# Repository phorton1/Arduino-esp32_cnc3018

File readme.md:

# Yet another cnc3018 Grbl Controller with WiFi and a TFT touch UI

This project has been interesting and is a waypoint on my path of understanding
and developing CNC machine controllers.  It is difficult to explain the decision
making process that led me here, or why I think it has been worth the investment
of time to arrive at this point, but I will try to touch on the main points.

Let's just start by saying I had *CNC fever*.  It started with *robots* but then
I had some stepper motors sitting around, and I wanted to make *something*, so
I built the **vMachine**.  While I was doing that I ordered a bunch of stuff to
make a variety of machines, including ordering two copies of the cheapest chinese 3018 CNC
machines I could find.

I had already long ago decided that I was going to use the ESP32 and (at that
time) the Grbl_Esp32 codebase for my machines.   The lure of a $5 dual processor
240Mhz SBC with Wifi and BT is just too much!   No way was I gonna use the Arduino
based controller that came with the machines.  So I was thinking about that the
entire time I was developing the vMachine.

Grbl_Esp32 was subsequently renamed to FluidNC, and I subsequently forked and
modified it to be usable as an extensible Arduino library. I had already also
started TFT UI development, and so these diverse aspects came together during
this project.

For me, one of the most interesting things about this project is the fact that
I used a prototype (breadboard) circuit while developing the machine to **mill
a controller board** for the machine itself!

Today I am just writing a quick readme to show off some of the machine's features
and steps in it's development.

## Prototype Circuit

I use these cool breadboards from [5e Board](https://www.5eboard.com/product-category/5e-circuit-boards/)
that allow me to create more complex and secure prototypes than with a normal breadboard.
Even then I decided early on that the spindle motor control and power supply should be on
a separate board, so I designed and implemented those parts on perf board.  They are visible
in the above photo.

The "test leads" in the above photo are for the z-axis **probe** which plays into the
development of the machine itself as the probe is used to develop the **mesh** for leveling
which is needed to obtain the z accuracy to mill the PC board.

## Limit Switches

The very first thing that everyone does to stock 3018's is adds limit switches.
So I 3D printed some mounts and stuck some limit switches on the machine. For
X and Y I just use the most ubiquitously available (cheapest!) switches, though
a bit large.  I went through multiple iterations on the Z axis, starting with
micro switches, but then relenting to using small (more expensive) lever switches.

Everything in grey plastic is my 3D printed additions to the machine (the black
plasatic is the original stuff).  The zAxis has a housing around the switches,
and an adjustable offset at the bottom (limit).  All the wires are shielded.

For the X and Y axis I originally started by using crimp on connectors that were
exposed, but didn't like them.  They kept falling off and the connectors were
too large for the wire I was using, so I 3D printed and constsructed my own connectors
using some thin brass sheet I've had sitting around for 20 years,

The crimp connectors were loose and easily fell off if you bumped them.
These connectors are secured with screws to ensure they don't fall off!

## Initial Sensor Board

I found pretty quickly that even with the nice breadboards, I was having
problems with the switches becasuse the leads on the resistors are small
and don't make good contact with breadboards.  So I created a perf board
version with the 74HC165 IO multiplexer chip and plugged it into the
breadboard:

## Milling the Controller Board

So, generally I got it working, but I was really anxious to eliminate the breadboard
and put a soldered board in place.   I was still getting problems due to the breadboard
and bad connections.

I had to learn a lot.  Spent time in  KiCad and Flatcam.   Designed it 10 times lol.
Cut some prototypes.  Learned a bit about applying and using green UV Solder Resist
Epoxy.

Finally got to where the following sequences of images looks practical :-)

1 - mill the board

In the end I had a pretty nice circuit board.  I will drill the holes after
doing the epoxy, so I then painted it with the green epoxy and exposed it
to the sun to cure the epoxy.

2 - mill the epoxy

OK, so I won't do this again!   It worked on this (v04) board, but subsquently
proved way too touchy to try to mill the UV epoxy off.  The copper layer is only
35/1000's of a millimeter ... like 2/1000's of an inch ... thick.   Even though
I added **mesh levelling** to the project, it is still nearly impossible to get
accurate enough to mill off the epoxy and NOT destroy the copper pads underneath.

The second photo above is actually a failure on an attempt to mill v05.
Most of the pads were destroyed because I was off by 1/100th of a millimeter!
Nonetheless it worked for this (V04) board and in the end I decided to use
V04 and move on.

I have ordered a UV laser.  My next idea is to expose the UV epoxy with the UV
laser on the cnc machine.  Photo masks are a bit complicated to work with!

3 - populate the board

Then it was pretty easy to solder on the headers, components, etc, and
I had a populated board.  It worked pretty much the first time!

I took a moment to take a photo of it with a light behind because it looks neat!

## Adding the touch screen

I put the board in the machine, and then used the machine to cut
another small circuit board to be used as a connector for the touch
screen:

After 3D printing an enclosure for it, and attaching it to the machine
(and reprinting it to add 5 ws2812b LEDs) I decided to write this page

Here is the final machine:

LOL, it still has the copper board from which I milled the LCD connector
on the work surface :-)

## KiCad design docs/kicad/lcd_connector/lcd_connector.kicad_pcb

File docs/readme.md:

# esp32_cnc3018 - Yet another cnc3018 Grbl Controller with WiFi and a TFT touch UI

**Home** --
**[History](history.md)** --
**[Hardware](hardware.md)** --
**[Electronics](electronics.md)** --
**[Software](software.md)** --
**[Installation](installation.md)** --
**[Version2](version2.md)**

esp32_cnc3018 is my implementation of an inexpensive 3-axis CNC machine that
makes use of the **ESP32** processor.  Essentially I bought the cheapest
3-axis CNC machine I could find on [Ebay](https://www.ebay.com/itm/392298131168), and then designed and implemented
my own controller board, limit switches, and extensions to that machine.

The ESP32 can easily be programmed from within the
Arduino development environment and has *dual cores*, runs at *240 Mhz* (as opposed to
the Arduino at 16Mhz) and comes with *520KB* (as opposed to 2KB) *of RAM*.  In addition
the ESP32 includes full onboard **WiFi and Bluetooth** capabilities, and can be had for
$5, or about half the price of a genuine Arduino.

Therefore my *primary design decision* was to base this, and my future CNC projects,
on an ESP32 processor.

**TODO: - VIDEO - introduction to the esp32_cnc3018**

TODO: Better picture of current esp32_cnc3018 (rename to Esp32_cnc3018)

The esp32_cnc3018 project is the 2nd machine in the line of open source
CNC machines I have created and published.  It provides a number of
features not commonly available in the lowest priced machines.

esp32_cnc3018 includes a full **Web Browser User Interface** so that it can be
controlled wirelessly from your phone or computer via **WiFi**.  It can also be controlled
via the **serial port** on the ESP32, via **Telnet** on port 23, or via **Bluetooth**
for usage with commonly available gcode sender programs.
Finally, it can also store gcode files on the optional **SD Card** and run jobs entirely
locally, right on the ESP32, via the optional
[**Touch Screen User Interface**](https://github.com/phorton1/Arduino-libraries-FluidNC_UI)
, without involving any other devices.

This repository includes all of the files and information needed to modify
a stock entry level CNC 3018 machine as I have. It includes the files needed to
**3D print** the plastic parts, as well as the underlying Fusion 360 designs
if you need or want to modify the 3D printed parts. It includes all of the **schematics**
and information needed to breadboard or otherwise create the electronic circuits,
as well as the KiCad files behind those, and the Flatcam and GCode files I used to
mill my own **circuit boards** for this machine.

This project continues a **general approach** to
building ESP32 based CNC machines of various types.
It is entirely based on the next generation
[FluidNC](https://github.com/bdring/FluidNC)
project, a hugely important codebase that I have
forked and modified slightly so-as to better be able build projects
within the Arduino IDE development environment.

<br>

## Documentation

The documentation starts with this page, and includes the following additional
pages:

- **[History](history.md)** - my personal historical **perspectives** and
  photos of the development process for the esp32_cnc3018 machine
- **[Hardware](hardware.md)** - shows the physical
  modifications to CNC 3018
- **[Electronics](electronics.md)** - the **schematics** and home made circuit
  boards for the machine.
- **[Software](software.md)** - describes the **software** architecture of
  esp32_cnc3018 and FluidNC
- **[Installation](Installation.md)** - instructions on **building** and installing
  the esp32_cnc3018 firmware onto the ESP32 using the Arduino IDE environment.

<br>

## Please Also See

Please also see my previous CNC machine based on the same architecture,
my implementation of a V-Plotter, the
[**vMachine**](https://github.com/phorton1/Arduino-_vMachine),
built entirely from scratch.

These "machines"  are relatively small INO programs.  They are built on top of a
number of other libraries that provide the bulk of the functionality.

- [**FluidNC**](https://github.com/phorton1/Arduino-libraries-FluidNC) - the next generation **ESP32 GRBL** machine
- [**FluidNC_UI**](https://github.com/phorton1/Arduino-libraries-FluidNC_UI) - a *touch screen user interface* for FluidNC
- [**FluidNC_Extensions**](https://github.com/phorton1/Arduino-libraries-FluidNC_Extensions) - some extensions to FluidNC

The core of the machine, the GRBL (g-code) interpreter, is based on the
[**FluidNC**](https://github.com/phorton1/Arduino-libraries-FluidNC)
library.  The operational details of the machine, what g-codes
are supported, the basic serial command protocol, the wifi and webserver,
the machine configuration, and most functional aspects of the machine are
provided by this library.

On top of FluidNC I have built
[**FluidNC_UI**](https://github.com/phorton1/Arduino-libraries-FluidNC_UI),
the *touch screen user interface*, as a library that can optionally
be used in ESP32 CNC projects.
Please see this library for a **description of the *User Interface***.

I have also added a
[**FluidNC_Extensions**](https://github.com/phorton1/Arduino-libraries-FluidNC_Extensions)
library that contains a number
of features that are used in this, and other machines based on this system.
This library contains methods and objects to abstract and extend the FluidNC
core.  Specific contents at this time include:

- some easy to use debug/info/error **output methods**
- methods to abstract the **state** of the FluidNC machine
- methods to abstract **control** of the FluidNC machine
- methods to supplement the FluidNC **configuration** system, and
- an implementation of **mesh bed levelling** as used in this esp32_cnc3018 machine

<br>

## Credits and License

This library is licensed under the
[GNU General Public License v3.0](https://github.com/phorton1/Arduino-esp32_cnc3018/tree/master/LICENSE.TXT)

**Credits**

- To **bdring** and the **FluidNC Team**

<br>
<hr>
<div style="text-align: right">
<a href='history.md'>NEXT</a><i> - more about esp32_cnc3018 ...</i>
</div>

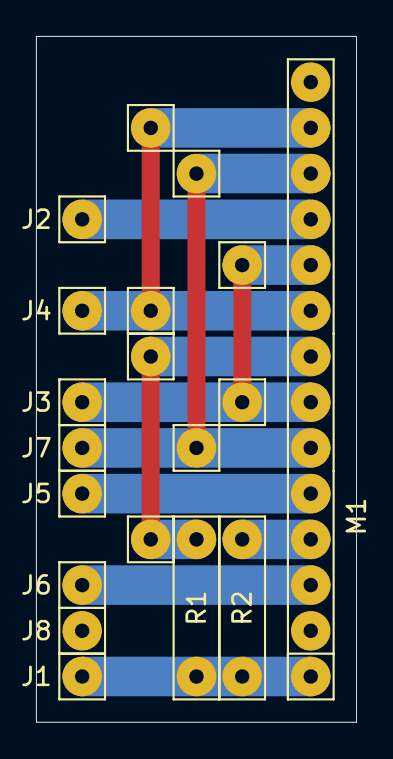
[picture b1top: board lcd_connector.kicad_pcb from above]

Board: 2 copper layers, 17.8 x 38.1 mm, 19 parts (0 on the bottom side), 10 nets.

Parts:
J1: 5V; my1pin
J2: T_CS; my1pin
J3: CLK; my1pin
J4: MISO; my1pin
J5: DC; my1pin
J6: CS; my1pin
J7: MOSI; my1pin
J8: GND; my1pin
M1: TFT_ILI9341; my14Pin
R1: 100; myResistor
R2: 10K; myResistor
V1, V2, V3, V5, V6, V7, V8, V9: Conn_01x01; my1pin

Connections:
unnamed: J1.1, M1.1, R1.1, R2.1
unnamed: J2.1, M1.11
unnamed: J3.1, M1.7, M1.10, V3.1, V5.1
unnamed: J4.1, M1.9, M1.13, V6.1, V8.1
unnamed: J5.1, M1.5
unnamed: J6.1, M1.3
unnamed: J7.1, M1.6, M1.12, V7.1, V9.1
unnamed: J8.1, M1.2
unnamed: M1.4, R2.2
unnamed: M1.8, R1.2, V1.1, V2.1

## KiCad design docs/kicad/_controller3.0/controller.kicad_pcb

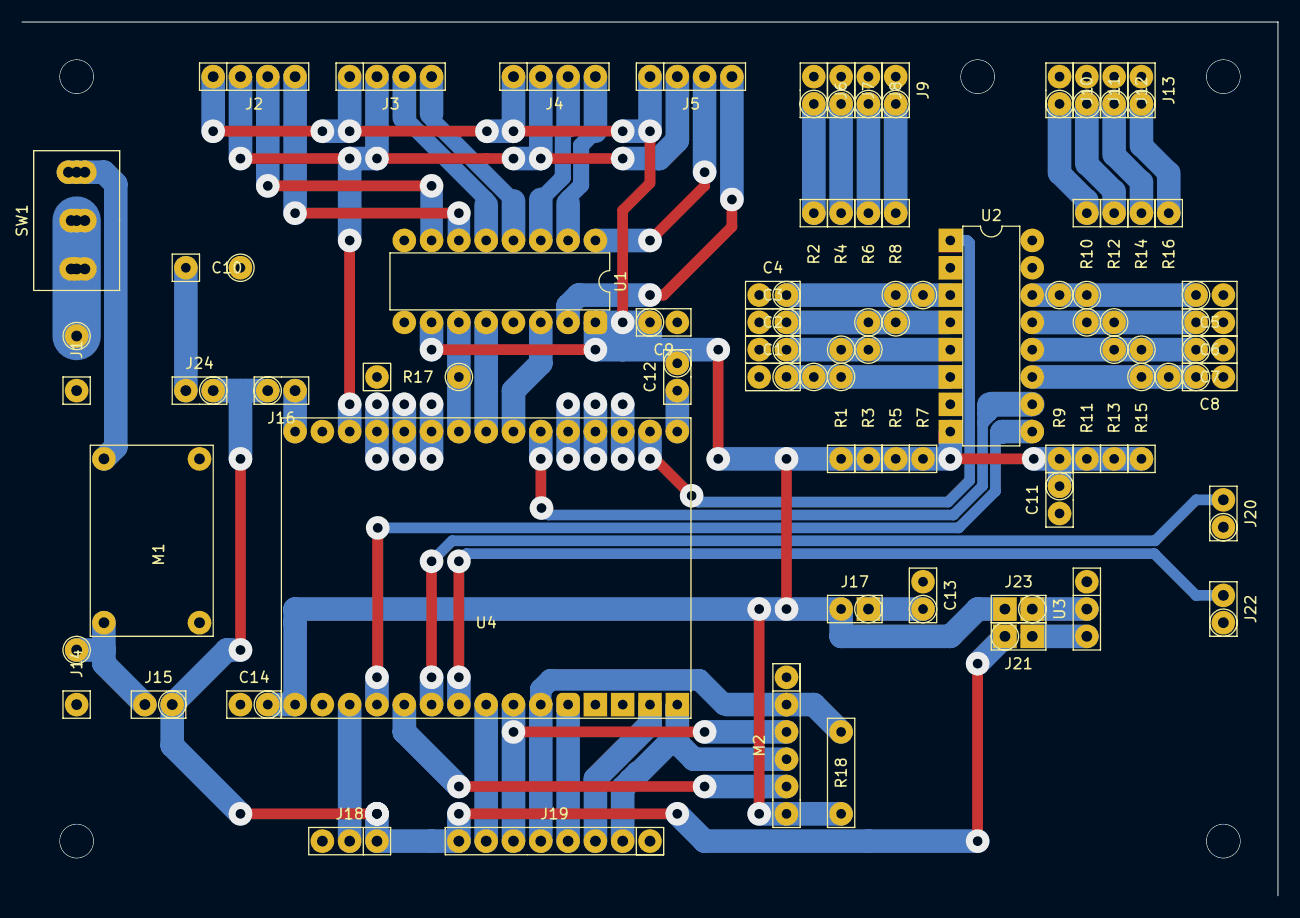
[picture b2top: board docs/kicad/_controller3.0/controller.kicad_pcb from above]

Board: 2 copper layers, 116.8 x 81.3 mm, 63 parts (0 on the bottom side), 53 nets.

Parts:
C1, C2, C3, C4, C5, C6, C7, C8, C9, C11, C14: 100nf; my2pin
C10: 330uf 50v; mySkip1
C12: 10uF; my2pin
C13: 220uf 10V; my2pin
J1: 24V; mySkip1
J2: X_AXIS; my4pin
J3: A_AXIS; my4pin
J4: Y_AXIS; my4pin
J5: Z_AXIS; my4pin
J6: X_ZERO; my2pin
J7: X_LIM; my2pin
J8: Y_ZERO; my2pin
J9: Y_LIM; my2pin
J10: Z_ZERO; my2pin
J11: Z_LIM; my2pin
J12: PROBE; my2pin
J13: UNUSED; my2pin
J14: 5V; mySkip1
J15: EXT 5V; my2pin
J16: USB 5V; my2pin
J17: CAP3V; my2pin
J18: WS2812B Strip; my3pin
J19: Display; my8Pin
J20: PWM_1A; my2pin
J21: REG5V; my2pin
J22: PWM_2A; my2pin
J23: REG3V; my2pin
J24: CAP5V; my2pin
M1: BUCK01
M2: SD_TYP0; my6Pin
R1, R15, R17: 10K; mySkip2
R2, R16: 100; mySkip5
R3, R13: 10K; mySkip3
R4, R14: 100; mySkip4
R5, R11: 10K; mySkip4
R6, R12: 100; mySkip3
R7, R9: 10K; mySkip5
R8, R10: 100; mySkip2
R18: 10K; myResistor
SW1: POWER; SW_DPDT_BLUE_LEVER
U1: 74HC595; myDip16
U2: 74HC165; myDip16
U3: LM1117; my3pin
U4: ESP32_DEV_0; ESP32-DEV_0

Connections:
+3V3: C9.1, C11.1, C12.1, C14.1, J2.1, J3.1, J4.1, J5.1, J17.2, J23.2, M2.6, R1.1, R3.1, R5.1, R7.1, R9.1, R11.1, R13.1, R15.1, R18.1, U1.10, U1.16, U2.8, U4.30
+5V: J15.1, J16.1, J18.1, J19.8, J21.1, J24.1
+24V: M1.4, SW1.1
A_DIR: J3.3, U1.5
A_STEP: J3.4, U1.4
GND: C1.2, C2.2, C3.2, C4.2, C5.2, C6.2, C7.2, C8.2, C9.2, C10.2, C11.2, C13.2, C14.2, J1.1, J6.2, J7.2, J8.2, J9.2, J10.2, J11.2, J12.2, J13.2, J14.1, J18.3, J19.1, J20.1, J22.1, M1.1, M1.2, M2.1, R17.1, U1.8, U1.13, U2.2, U2.7, U2.16, U3.1, U4.2, U4.29
I2S_BCK: R17.2, U1.11, U4.7
I2S_DATA: U1.14, U4.9
I2S_WS: U1.12, U4.8
LED: J18.2, U4.28
MCLK: J19.6, M2.3, U4.22
MISO: J19.5, M2.2, R18.2, U4.21
MOSI: J19.2, M2.4, U4.16
unnamed: C1.1, R1.2, R2.2, U2.6
unnamed: C2.1, R3.2, R4.2, U2.5
unnamed: C3.1, R5.2, R6.2, U2.4
unnamed: C4.1, R7.2, R8.2, U2.3
unnamed: C5.1, R9.2, R10.2, U2.14
unnamed: C6.1, R11.2, R12.2, U2.13
unnamed: C7.1, R13.2, R14.2, U2.12
unnamed: C8.1, R15.2, R16.2, U2.11
unnamed: C10.1, J24.2
unnamed: C12.2, U4.15
unnamed: C13.1, J17.1
unnamed: J1.2, SW1.2, SW1.3
unnamed: J6.1, R2.1
unnamed: J7.1, R4.1
unnamed: J8.1, R6.1
unnamed: J9.1, R8.1
unnamed: J10.1, R10.1
unnamed: J11.1, R12.1
unnamed: J12.1, R14.1
unnamed: J13.1, R16.1
unnamed: J14.2, J15.2, M1.3
unnamed: J16.2, U4.1
unnamed: J21.2, U3.3
unnamed: J23.1, U3.2
PWM_1: J20.2, U4.25
PWM_2: J22.2, U4.24
SD_CS: M2.5, U4.26
STEP_EN: J2.2, J3.2, J4.2, J5.2, U4.3
SW_CLK: U2.10, U4.10
SW_DATA: U2.1, U4.14
SW_LATCH: U2.9, U4.27
TFT_CS: J19.3, U4.17
TFT_DC: J19.4, U4.20
TOUCH_CS: J19.7, U4.23
X_DIR: J2.3, U1.7
X_STEP: J2.4, U1.6
Y_DIR: J4.3, U1.3
Y_STEP: J4.4, U1.2
Z_DIR: J5.3, U1.1
Z_STEP: J5.4, U1.15

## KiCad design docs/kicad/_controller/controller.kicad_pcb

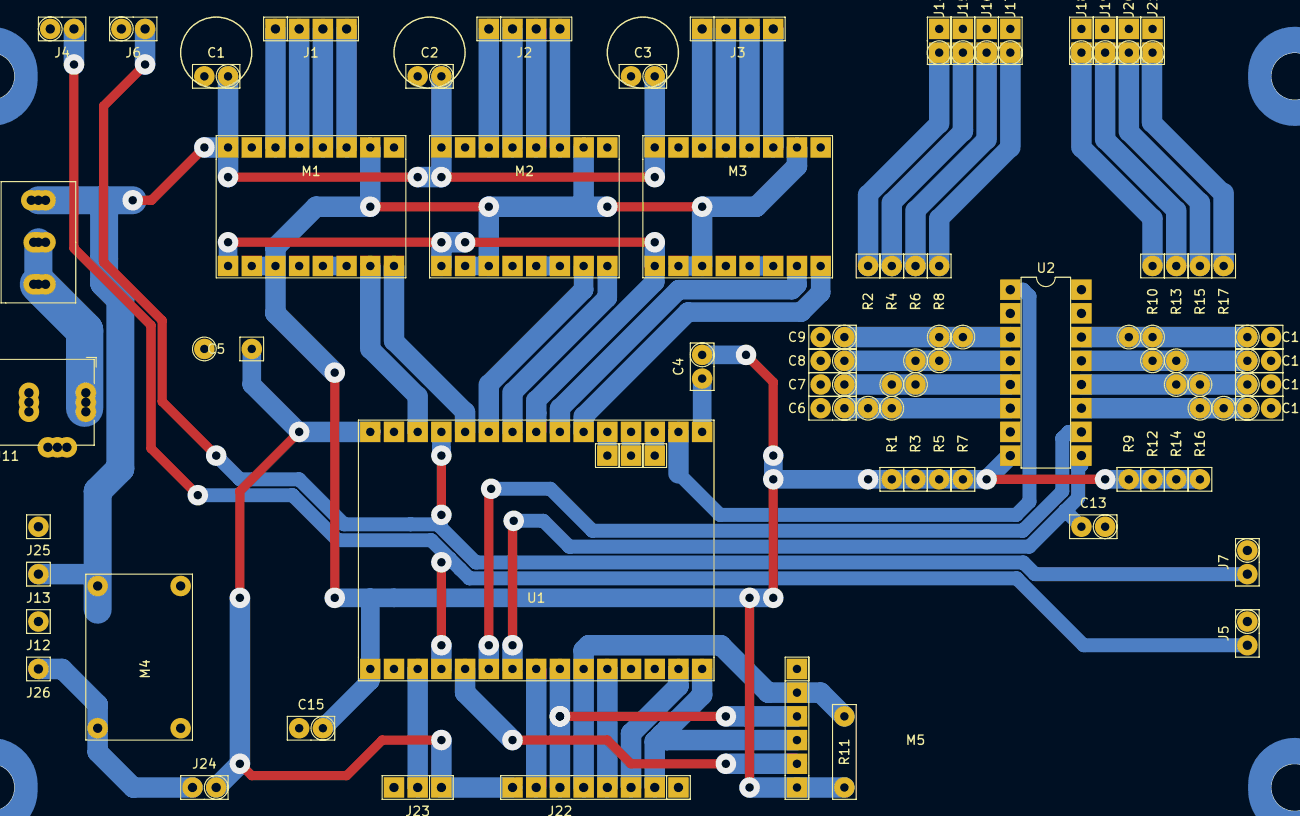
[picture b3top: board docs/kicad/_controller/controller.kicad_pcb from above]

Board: 2 copper layers, 66 parts (0 on the bottom side), 61 nets.

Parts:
C1, C2, C3: 100uf; my2pin
C4: 10uF; my2pin
C5: 330uf 50v; mySkip1
C6, C7, C8, C9, C10, C11, C12, C14: 100nf; my2pin
C13: 472nf; my2pin
C15: 220uf 10V; my2pin
J1: X_AXIS; my4pin
J2: Y_AXIS; my4pin
J3: Z_AXIS; my4pin
J4: PWM_1A; my2pin
J5: PWM_1B; my2pin
J6: PWM_2A; my2pin
J7: PWM_2B; my2pin
J8, J9, J10, J12, J13, J25, J26: bbb; my1pin
J11: Jack-DC; myBarrelJack
J14: X_ZERO; my2pin
J15: X_LIM; my2pin
J16: Y_ZERO; my2pin
J17: Y_LIM; my2pin
J18: Z_ZERO; my2pin
J19: Z_LIM; my2pin
J20: PROBE; my2pin
J21: UNUSED; my2pin
J22: Display; my8Pin
J23: WS2812B Strip; my3pin
J24: 5V Jumper; my2pin
M1, M2, M3: A4988; a498
M4: BUCK01
M5: SD_TYP0; my6Pin
R1: 6.8K actual; mySkip2
R2: 220 Actual; mySkip5
R3, R14: 10K; mySkip3
R4, R15: 100; mySkip4
R5, R12: 10K; mySkip4
R6, R13: 100; mySkip3
R7, R9: 10K; mySkip5
R8, R10: 100; mySkip2
R11: 10K; myResistor
R16: 10K; mySkip2
R17: 100; mySkip5
SW1: POWER; SW_DPDT_BLUE_LEVER
U1: ESP32_DEV_0; ESP32-DEV_0
U2: 74HC165; myDip16

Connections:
+3V3: C4.1, C15.1, M1.6, M1.7, M1.15, M2.6, M2.7, M2.15, M3.6, M3.7, M3.15, M5.6, R1.1, R3.1, R5.1, R7.1, R9.1, R11.1, R12.1, R14.1, R16.1, U1.30, U2.8
+5V: C5.1, J22.8, J23.1, J24.1, U1.1
+24V: C1.1, C2.1, C3.1, J13.1, M1.9, M2.9, M3.9, M4.4, SW1.1
GND: C1.2, C2.2, C3.2, C5.2, C6.2, C7.2, C8.2, C9.2, C10.2, C11.2, C12.2, C13.1, C14.2, C15.2, J4.1, J5.1, J6.1, J7.1, J11.2, J12.1, J14.2, J15.2, J16.2, J17.2, J18.2, J19.2, J20.2, J21.2, J22.1, J23.3, J25.1, M1.10, M1.16, M2.10, M2.16, M3.10, M3.16, M4.1, M4.2, M5.1, U1.2, U1.29, U2.2, U2.7, U2.16
LED: J23.2, U1.28
MCLK: J22.6, M5.3, U1.22
MISO: J22.5, M5.2, R11.2, U1.21
MOSI: J22.2, M5.4, U1.16
unnamed: C4.2, U1.15
unnamed: C6.1, R1.2, R2.2, U2.6
unnamed: C7.1, R3.2, R4.2, U2.5
unnamed: C8.1, R5.2, R6.2, U2.4
unnamed: C9.1, R7.2, R8.2, U2.3
unnamed: C10.1, R9.2, R10.2, U2.14
unnamed: C11.1, R12.2, R13.2, U2.13
unnamed: C12.1, R14.2, R15.2, U2.12
unnamed: C14.1, R16.2, R17.2, U2.11
unnamed: J1.1, M1.11
unnamed: J1.2, M1.12
unnamed: J1.3, M1.13
unnamed: J1.4, M1.14
unnamed: J2.1, M2.11
unnamed: J2.2, M2.12
unnamed: J2.3, M2.13
unnamed: J2.4, M2.14
unnamed: J3.1, M3.11
unnamed: J3.2, M3.12
unnamed: J3.3, M3.13
unnamed: J3.4, M3.14
unnamed: J8.1, U1.11
unnamed: J9.1, U1.12
unnamed: J10.1, U1.13
unnamed: J11.1, SW1.2, SW1.3
unnamed: J14.1, R2.1
unnamed: J15.1, R4.1
unnamed: J16.1, R6.1
unnamed: J17.1, R8.1
unnamed: J18.1, R10.1
unnamed: J19.1, R13.1
unnamed: J20.1, R15.1
unnamed: J21.1, R17.1
unnamed: J24.2, J26.1, M4.3
unnamed: M1.3, M1.4
unnamed: M2.3, M2.4
unnamed: M3.3, M3.4
PWM_1: J4.2, J5.2, U1.27
PWM_2: J6.2, J7.2, U1.4
SD_CS: M5.5, U1.26
STEP_EN: M1.8, M2.8, M3.8, U1.8
SW_CLK: U1.25, U2.10
SW_DATA: U1.14, U2.1
SW_LATCH: C13.2, U1.24, U2.9
TFT_CS: J22.3, U1.17
TFT_DC: J22.4, U1.20
TOUCH_CS: J22.7, U1.23
X_DIR: M1.1, U1.5
X_STEP: M1.2, U1.3
Y_DIR: M2.1, U1.7
Y_STEP: M2.2, U1.6
Z_DIR: M3.1, U1.10
Z_STEP: M3.2, U1.9

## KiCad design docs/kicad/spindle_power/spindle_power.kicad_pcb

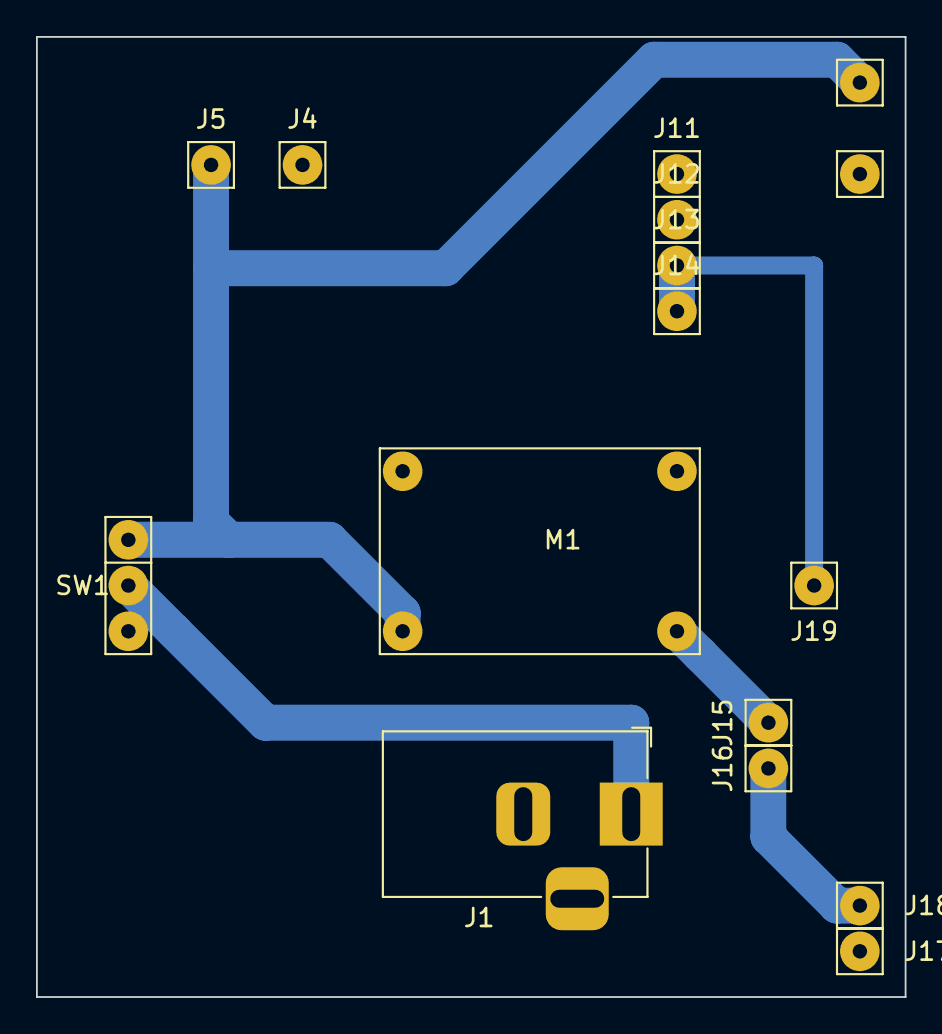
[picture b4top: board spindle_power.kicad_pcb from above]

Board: 2 copper layers, 48.3 x 53.3 mm, 16 parts (0 on the bottom side), 6 nets.

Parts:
J1: Jack-DC; myBarrelJack
J2: 24V-; my1pin
J3: 24V+; my1pin
J4: SP_BOARD-; my1pin
J5: SP_BOARD+; my1pin
J11, J12: SPWM_GND; my1pin
J13, J14: SPWM; my1pin
J15: JMP1; my1pin
J16: JMP2; my1pin
J17: OUT-; my1pin
J18: OUT+; my1pin
J19: PWM; my1pin
M1: BUCK01
SW1: ON_OFF; my3pin

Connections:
unnamed: J1.1, SW1.2
unnamed: J1.2, J2.1, J4.1, J11.1, J12.1, J17.1, M1.1, M1.2
unnamed: J3.1, J5.1, M1.4, SW1.1
unnamed: J13.1, J14.1, J19.1
unnamed: J15.1, M1.3
unnamed: J16.1, J18.1

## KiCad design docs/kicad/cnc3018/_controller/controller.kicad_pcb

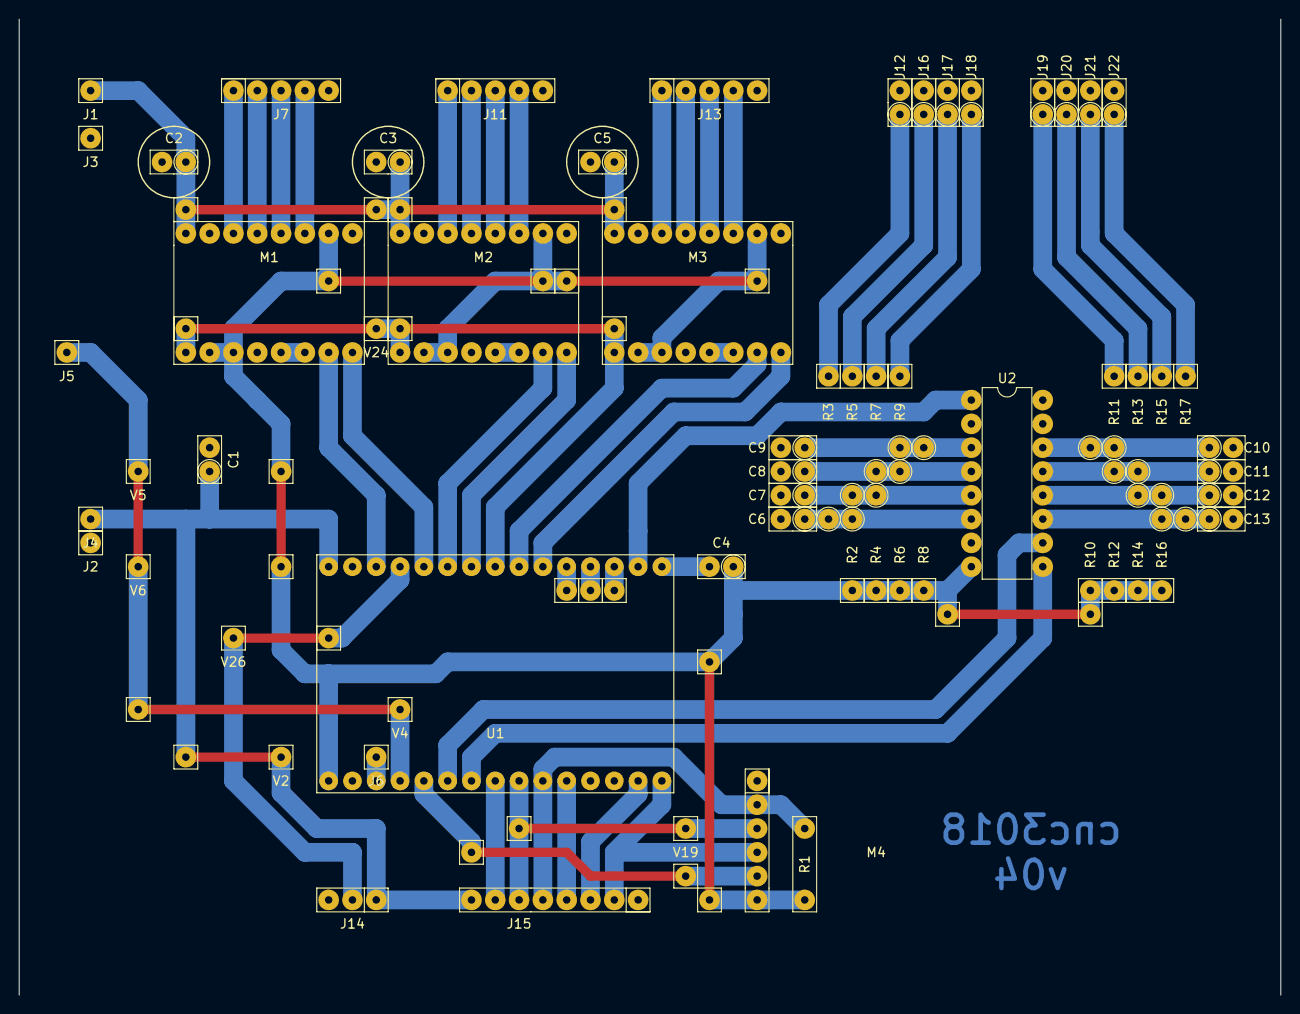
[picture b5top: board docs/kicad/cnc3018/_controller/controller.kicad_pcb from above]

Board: 2 copper layers, 134.6 x 104.1 mm, 88 parts (0 on the bottom side), 59 nets.

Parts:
C1: 33uf; my2pin
C2, C3, C5: 100uf; my2pin
C4: 10uF; my2pin
C6, C7, C8, C9, C10, C11, C12, C13: 100nf; my2pin
J1: 24V; my1pin
J2, J3: GND; my1pin
J4: 5V; my1pin
J5: SPIN; my1pin
J6, J8, J9, J10: bbb; my1pin
J7: X; my5Pin
J11: Y; my5Pin
J12: X_ZERO; my2pin
J13: Z; my5Pin
J14: WS2812B Strip; my3pin
J15: Display; my8Pin
J16: X_LIM; my2pin
J17: Y_ZERO; my2pin
J18: Y_LIM; my2pin
J19: Z_ZERO; my2pin
J20: Z_LIM; my2pin
J21: PROBE; my2pin
J22: UNUSED; my2pin
M1, M2, M3: A4988; a498
M4: SD_TYP0; my6Pin
R1: 10K; myResistor
R2, R16: 10K; mySkip2
R3, R17: 100; mySkip5
R4, R14: 10K; mySkip3
R5, R15: 100; mySkip4
R6, R12: 10K; mySkip4
R7, R13: 100; mySkip3
R8, R10: 10K; mySkip5
R9, R11: 100; mySkip2
U1: ESP32_DEV_0; ESP32-DEV_0
U2: 74HC165; myDip16
V1: v30; my1pin
V2: v31; my1pin
V3: v40; my1pin
V4: v41; my1pin
V5: v42; my1pin
V6: v43; my1pin
V7: v14; my1pin
V8: v15; my1pin
V9: v16; my1pin
V10: v17; my1pin
V11: v18; my1pin
V12: v19; my1pin
V13: v10; my1pin
V14: v00; my1pin
V15: v20; my1pin
V16: v60; my1pin
V17: v61; my1pin
V18: v70; my1pin
V19: v71; my1pin
V20: v01; my1pin
V21: v11; my1pin
V22: v12; my1pin
V23: v02; my1pin
V24: v21; my1pin
V25: v22; my1pin
V26: v50; my1pin
V27: v51; my1pin
V28: v13; my1pin
V29: v23; my1pin
V30: v03; my1pin

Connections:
unnamed: C1.1, J4.1, J14.1, J15.8, U1.1, V1.1, V2.1
unnamed: C1.2, C2.2, C3.2, C5.2, C6.2, C7.2, C8.2, C9.2, C10.2, C11.2, C12.2, C13.2, J2.1, J3.1, J7.5, J11.5, J12.2, J13.5, J14.3, J15.1, J16.2, J17.2, J18.2, J19.2, J20.2, J21.2, J22.2, M1.10, M1.16, M2.10, M2.16, M3.10, M3.16, M4.1, U1.2, U1.29, U2.2, U2.7, U2.16
unnamed: C2.1, C3.1, C5.1, J1.1, M1.9, M2.9, M3.9, V14.1, V20.1, V23.1, V30.1
unnamed: C4.1, M1.6, M1.7, M1.15, M2.6, M2.7, M2.15, M3.6, M3.7, M3.15, M4.6, R1.1, R2.1, R4.1, R6.1, R8.1, R10.1, R12.1, R14.1, R16.1, U1.30, U2.8, V7.1, V8.1, V9.1, V10.1, V11.1, V12.1, V13.1, V21.1, V22.1, V28.1
unnamed: C4.2, U1.15
unnamed: C6.1, R2.2, R3.2, U2.6
unnamed: C7.1, R4.2, R5.2, U2.5
unnamed: C8.1, R6.2, R7.2, U2.4
unnamed: C9.1, R8.2, R9.2, U2.3
unnamed: C10.1, R10.2, R11.2, U2.14
unnamed: C11.1, R12.2, R13.2, U2.13
unnamed: C12.1, R14.2, R15.2, U2.12
unnamed: C13.1, R16.2, R17.2, U2.11
unnamed: J5.1, U1.27, V3.1, V4.1, V5.1, V6.1
unnamed: J6.1, U1.28
unnamed: J7.1, M1.11
unnamed: J7.2, M1.12
unnamed: J7.3, M1.13
unnamed: J7.4, M1.14
unnamed: J8.1, U1.11
unnamed: J9.1, U1.12
unnamed: J10.1, U1.13
unnamed: J11.1, M2.11
unnamed: J11.2, M2.12
unnamed: J11.3, M2.13
unnamed: J11.4, M2.14
unnamed: J12.1, R3.1
unnamed: J13.1, M3.11
unnamed: J13.2, M3.12
unnamed: J13.3, M3.13
unnamed: J13.4, M3.14
unnamed: J14.2, U1.4, V26.1, V27.1
unnamed: J15.2, M4.4, U1.16
unnamed: J15.3, U1.17
unnamed: J15.4, U1.20
unnamed: J15.5, M4.2, R1.2, U1.21
unnamed: J15.6, M4.3, U1.22, V18.1, V19.1
unnamed: J15.7, U1.23
unnamed: J16.1, R5.1
unnamed: J17.1, R7.1
unnamed: J18.1, R9.1
unnamed: J19.1, R11.1
unnamed: J20.1, R13.1
unnamed: J21.1, R15.1
unnamed: J22.1, R17.1
unnamed: M1.1, U1.5
unnamed: M1.2, U1.3
unnamed: M1.3, M1.4
unnamed: M1.8, M2.8, M3.8, U1.8, V15.1, V24.1, V25.1, V29.1
unnamed: M2.1, U1.7
unnamed: M2.2, U1.6
unnamed: M2.3, M2.4
unnamed: M3.1, U1.10
unnamed: M3.2, U1.9
unnamed: M3.3, M3.4
unnamed: M4.5, U1.26, V16.1, V17.1
unnamed: U1.14, U2.1
unnamed: U1.24, U2.9
unnamed: U1.25, U2.10

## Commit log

2021-08-26 initial commit after breakout from Arduino
2021-08-26 MESH DONE - implemented "kinematics" for mesh, configurable variables, yaml_overrides.
2021-08-28 Analysis of existing Grbl_Esp32 gcodes
2021-08-28 Made mesh absolute and persistent, implemented realtime zoffset
2021-09-15 changed input pin mapping and moved pins to cnc3018.h
2021-09-15 implemented averaging mesh probes
2021-09-18 updated pins for new board
2021-09-19 Turn on UI, add pinout comments
2021-09-22 cleanup switches, add meaningful ws2812b leds, pinout comments
2021-09-23 -- REBASE to FluidNC --
2021-09-23 rename Grbl_Esp32 to FluidNC
2021-09-23 initial readme work
2021-09-24 docs - initial 3d printing and electronics md files
2021-09-24 change v2812b.h to my_ws2812b.h
2021-09-24 fix broken link
2021-09-24 moved Mesh to FluidNC_extensions, standardized FluidDebug.h, and renamed UI test program
2021-09-24 comment only
2021-09-25 implement basic HOME and SET UI dlg windows and functionality
2021-09-26 implement UI messh settings
2021-09-27 prep for consolidation of gStatus
2021-09-27 introduced gActions.h/cpp and restructured code all my code to NOT include a plethora of FluidNC h files
2021-09-28 implemented live_z and mesh z UI, tested
2021-10-01 updated Yaml file for SpindleControl2
2021-10-11 New Spindle Control; Added 500mw 405nm laser, debugging
2021-10-14 renamed to CNC3018_ESP
2021-10-14 renamed to CNC3018_EPS and moved readme.md to /docs
2021-10-14 untested rework of YAML and installation.md
2021-10-15 documentation WIP
2021-10-16 documentation WIP - LICENSE.TXT
2021-10-16 documentation tree license & credits
2021-10-16 got rid of sofware.md readme files*
2021-10-16 update CNC3018_ESP and other denormalized kiCad stuff*
2021-10-16 added youtube TODO's
2021-10-17 finish merge with _main branch of my fork of FluidNC project
2021-10-17 documentation - update to new pcb_mount, rename fusion files
2021-10-20 SCREEN_GRAB - implemented FluidNC_UI gApplication doScreenGrab and console.pm to write BMP files
2021-10-20 repair nmissed yaml changes to PWM speeds and frequency
2021-10-20 documentation - added some animated gifs, started UI docs
2021-10-21 documentation WIP - added ctrl-O 'pending screen grab' realtime command
2021-10-21 documentation WIP: TFT_eSPI and FluidNC_UI and screen grabs
2021-10-21 documentation: broken links and image filenames
2021-10-22 documentation
2021-10-23 spellcheck
2021-10-23 cleanup cnc3018 before software doc*
2021-10-23 renamed CNC3028_ESP to esp32_cnc3018
2021-10-25 wip checkin of FluidNC SERIN SerialInput pins vs my switches.cpp and myProbe.h/cpp
2021-10-25 CLEANUP - using SERI pins, got rid of myProbe and changed "switches.cpp" to "my_pixels.cpp" since that's all it does now.
2021-10-25 preference.txt
2021-10-26 implemented I2SI bus and changed SERI to I2SI - not yet tested with cap on cnc3018, nor synchronized
2021-10-27 added capacitor and tested I2SI on cnc3018
2021-10-27 changed debug messages
2021-10-28 minor edits
2021-10-28 file accidentally moved
2021-10-29 I2SI WIP
2021-10-29 doc touches
2021-10-29 flesh out FluidNC_extensions readme.md*
2021-10-31 change SDCard startup messages to INFO
2021-12-23 added laser.yaml
2022-03-04 kicad controller board v2.0 and smaller lcd_connector
2022-03-06 version 2 PCB and smaller LCD connector
2022-03-12 working on CNC_3018 v2
2022-03-22 new WebUI that supports Adler-32 upload checksums
2022-03-28 added cnc20mm v3 PCB
2022-03-28 updated index.html.gz to use checksums for sd file uploads
2022-03-28 initial test cnc20mm (v3) before branch
2022-03-28 prefs.txt
2022-03-28 remove CNC_MACHINE_NUM after branching cnc20mm
2022-04-10 renamed cnc3018.yaml to config_v1.yaml, got rid of laser.yaml noting that they are the same if no PWM spindle
2022-04-10 smaller lcd_connector
2022-04-14 got rid of kludge delay for debug output in task header (now that logging.cpp is synchronized)
2022-04-15 implement FluidNC_UI driver/size/rotation API - rename tft calibration data files
2022-04-15 remove unused YELLOW case from pixels
2022-04-15 UPDATED V1 and V2 to latest version - added (uneeded) default parameters to FluidNC_UI_init() and set build to ArduinoBuilds
2022-08-01 changed MACHINE_NUMBER to 1 to build cnc3018 #1
2022-08-15 build and upload V2
2023-01-12 got rid of obsolete controller boards and "spindle" kicad stuff
2023-01-12 renamed kicad "_controller2.0" to "controller"
2023-07-17 docs - add empty V2 page
2023-07-27 docs - added a dash to the header
2023-11-02 fix broken links across all repos with introduction of base-apps-gitUI::repoDocs.pm
2024-09-15 tried building with ESP32 Core 3_0_4, saved preferences and list of errors
2024-11-07 refork NMEA2000 libraries; cleanup FluidNC_Extensions::mesh.cpp() and cnc3018.h CNC_MACHINE, UI_WITH_MESH and USE_LARGE Mesh defines and compile messages - turning off default definition of UI_WITH_M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
2025-02-14 added new "foot" 3d printed object and "dial indicator" bracket for 3018 re-level (new wasteboard)
2025-02-17 built 300w controller box
2025-02-18 changed x * y pullofs from 5mm to 2mm for tight cnc3018
2025-02-25 new base * wasteboard table for cnc3018
